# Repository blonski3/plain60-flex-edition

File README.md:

# Plain60 MX+ALPS Flex Edition rev2.2

This universal 60% PCB is designed to support as little layouts as possible without limiting usability for most users. The reason I did this is because other PCBs made for this form factor usually have so many supported layouts that it could almost qualify as swiss cheese.

It also features a fuse and an ESD protection chip to protect the MCU and other parts of the PCB.

## Features
- Fits in the TGR Unikorn
- Compatible with QMK Firmware and VIA Configurator (if you flash a VIA compatible .hex file)
- Compatible with most universal 60% cases and HHKB/WKL Tofu by KBDfans
- USB type-C
- Optional JST header for connection with daughterboard
- Footprint for optional speaker (AST1109MLTRQ)
- ESD protection and fuse
- No LEDs and no underglow
- Minimal layout support
- ISP header

## Supported layouts

## Building
If you feel like building a few of these PCBs yourself, go to the 'Releases' tab and download the latest gerber files. Order those at your favourite PCB manufacturer, get the components needed (see below) and solder them on! A hot air station is not required but a soldering iron is. Flux is recommended.

## Opening the project
To open the files you will need the latest KiCAD nightly version.

## Bill of materials (BOM)
Amount is per PCB, multiply as needed.

| LCSC part # | Description   | Value | Package  | Amount |
| ----------- | ------------- | ----- | -------- | ------:|
| C128353     | Capacitor     | 0.1uF | 0805     | 4      |
| C131056     | Capacitor     | 4.7uF | 0805     | 1      |
| C215803     | Capacitor     | 1uF   | 0805     | 1      |
| C109001     | Diode         |       | 0805     | 65     |
| C261942     | Fuse          |       | 0805     | 1      |
| C165948     | Connector     |       | SMD/THT  | 1      |
| C103904     | Resistor      | 10K   | 0805     | 2      |
| C212411     | Resistor      | 5.1K  | 0805     | 2      |
| C325772     | Resistor      | 22    | 0805     | 2      |
| C44854      | MCU           | 32U4  | QFP-44   | 1      |
| C7519       | ESD chip      |       | SOT23-6  | 1      |
| C341521     | Resonator     | 16MHz | SMD      | 1      |
| C92584      | Switch        |       | SMD      | 1      |
| C160404     | Optional JST  |       | SMD      | 1      |

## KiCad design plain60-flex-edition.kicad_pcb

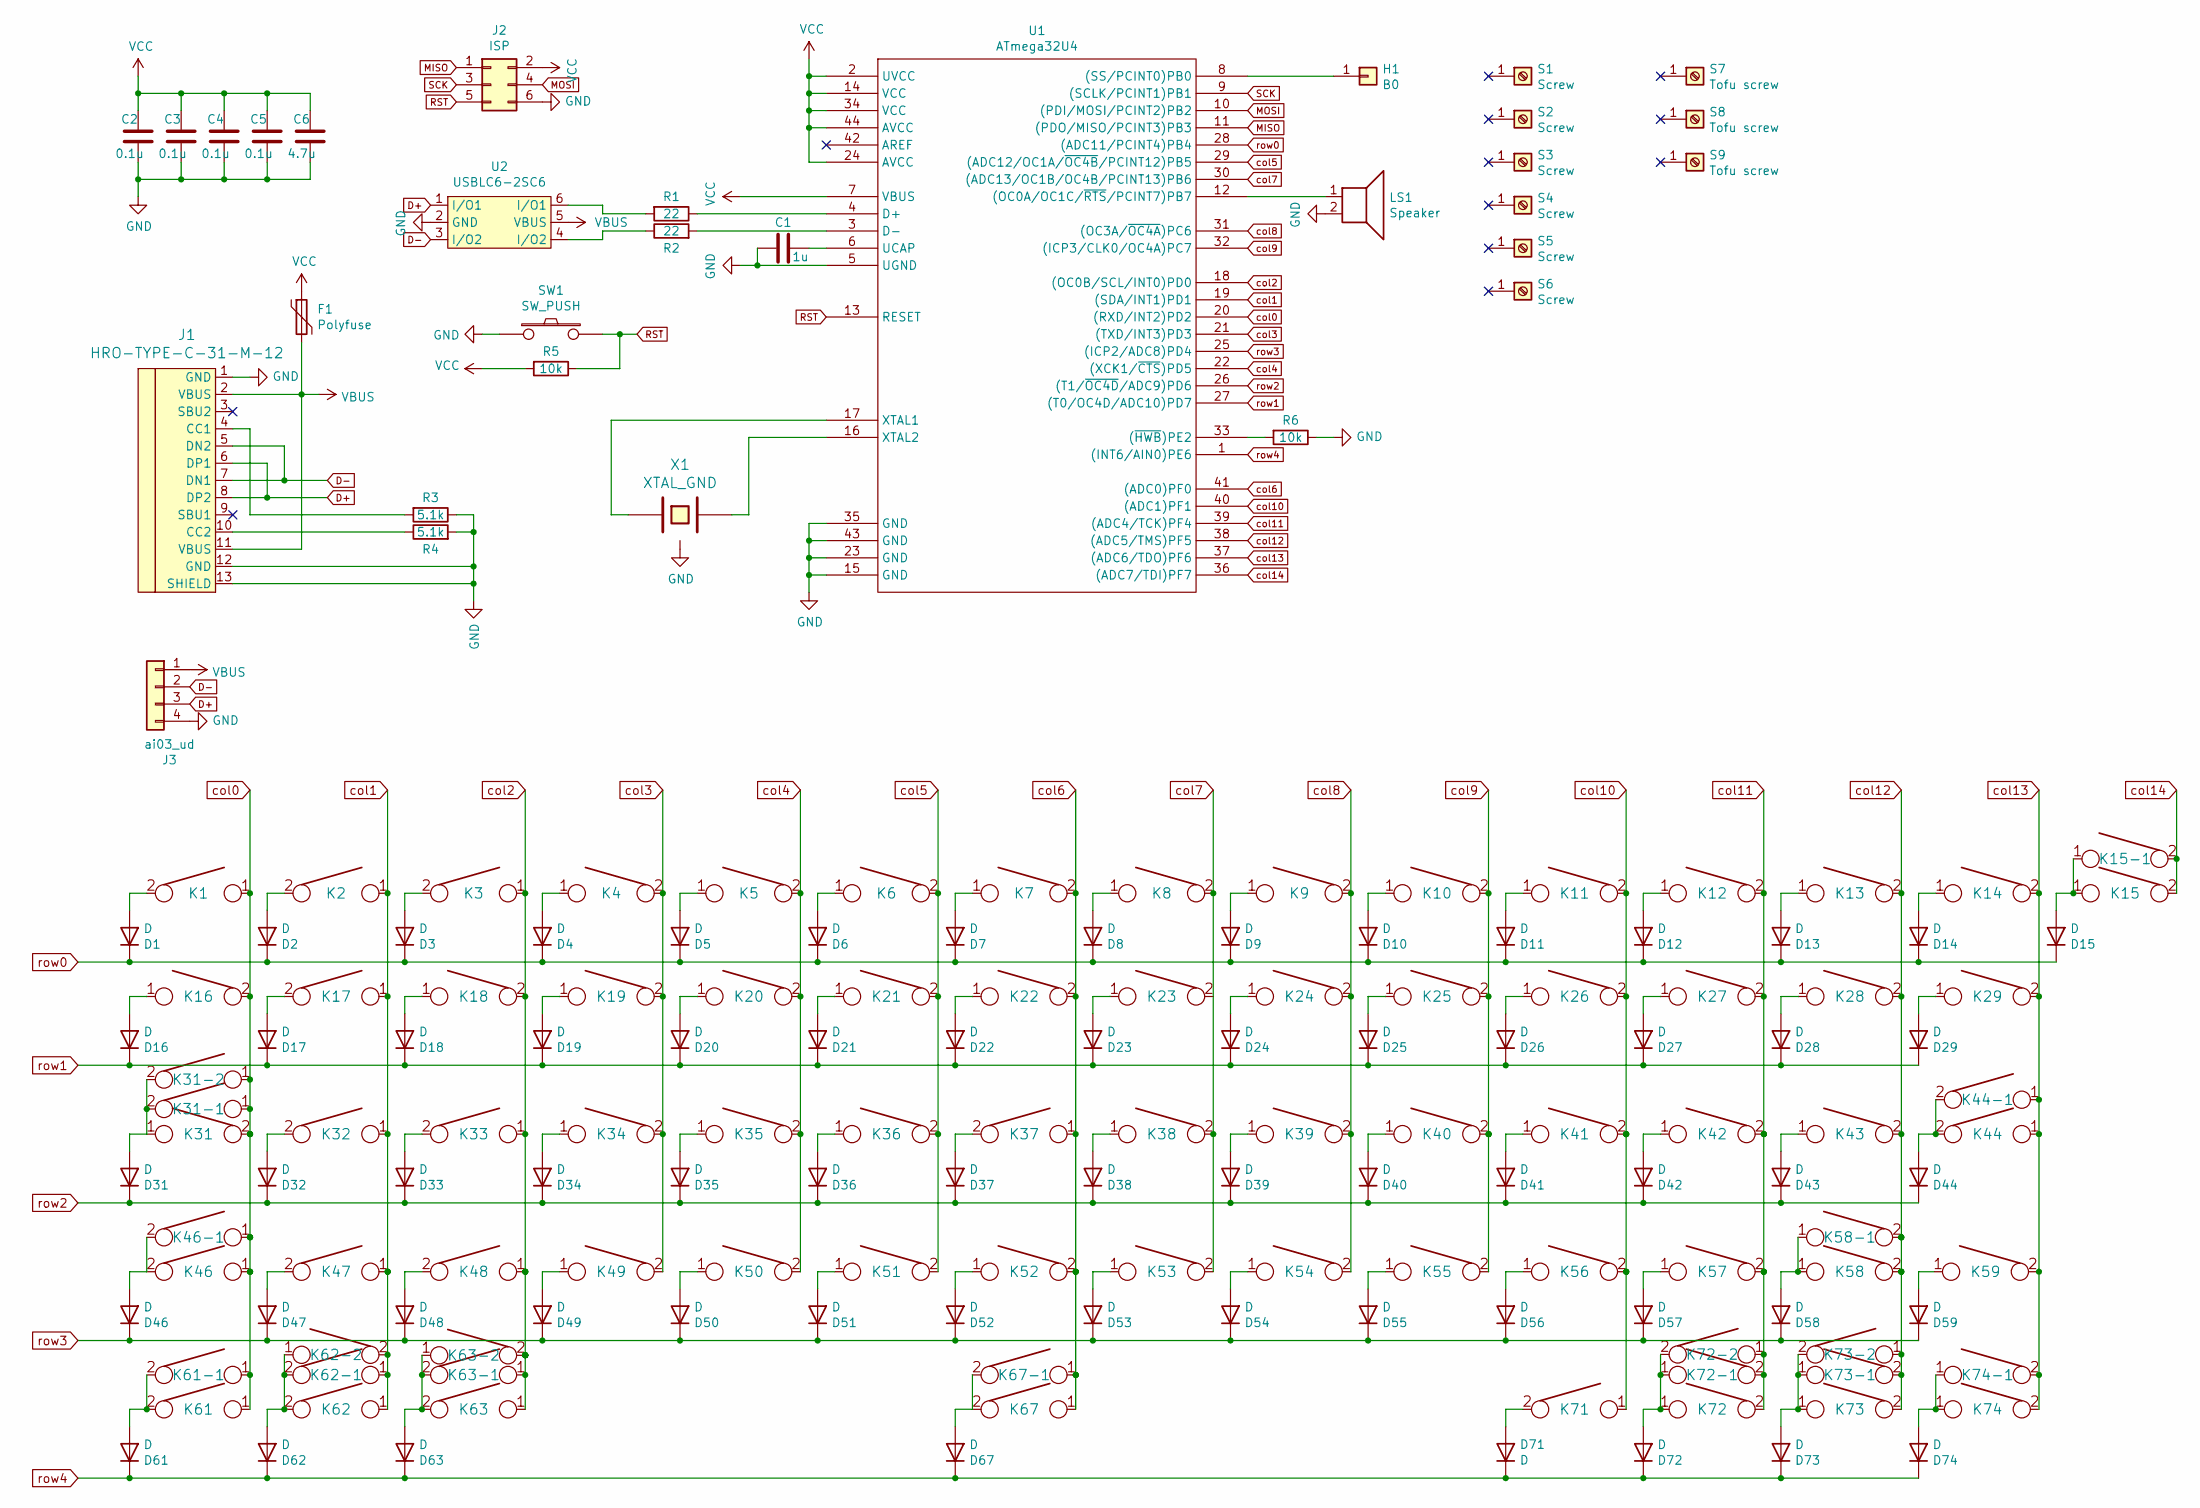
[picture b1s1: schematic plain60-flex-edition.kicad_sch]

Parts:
C1: 1u; C_0805
C2, C3, C4, C5: 0.1u; C_0805
C6: 4.7u; C_0805
D1, D2, D3, D4, D5, D6, D7, D8, D9, D10, D11, D12, D13, D14, D15, D16, D17, D18, D19, D20, D21, D22, D23, D24, D25, D26, D27, D28, D29, D31, D32, D33, D34, D35, D36, D37, D38, D39, D40, D41, D42, D43, D44, D46, D47, D48, D49, D50, D51, D52, D53, D54, D55, D56, D57, D58, D59, D61, D62, D63, D67, D71, D72, D73, D74: D; D_0805
F1: Polyfuse; R_0805
H1: B0; free_pin
J1: HRO-TYPE-C-31-M-12
J2: ISP; isp_standard
J3: ai03_ud; JST_SH_SM04B-SRSS-TB_1x04-1MP_P1.00mm_Horizontal
K1, K2, K3, K4, K5, K6, K7, K8, K9, K10, K11, K12, K13, K14, K15-1, K17, K18, K19, K20, K21, K22, K23, K24, K25, K26, K27, K28, K32, K33, K34, K35, K36, K37, K38, K39, K40, K41, K42, K47, K48, K49, K50, K51, K52, K53, K54, K55, K56, K57, K59, K62-1, K73-1: KEYSW; MX-1U-NoLED
K15: KEYSW; MX-2U-NoLED
K16, K29, K43, K61-1, K63-1, K72-1, K74-1: KEYSW; MX-1.5U-NoLED
K31, K58-1: KEYSW; MX-1.75U-NoLED
K31-1, K46-1, K61, K62, K63, K71, K72, K73, K74: KEYSW; MX-1.25U-NoLED
K31-2, K63-2, K72-2: KEYSW; ALPS-1.5U
K44, K46: KEYSW; MX-2.25U-NoLED
K44-1: KEYSW; MX-ISO-FLIPPED-ReversedStabilizers
K58: KEYSW; MX-2.75U-NoLED
K62-2, K73-2: KEYSW; ALPS-1.25U
K67: KEYSW; MX-6.25U-ReversedStabilizers-NoLED
K67-1: KEYSW; MX-7U-ReversedStabilizers-NoLED
LS1: Speaker; speaker_AST1109MLTRQ
R1, R2: 22; R_0805
R3, R4: 5.1k; R_0805
R5, R6: 10k; R_0805
S1, S2, S3, S6: Screw; 5.5_5x2.5mm
S4, S5: Screw; 10x5_7x2.5mm
S7, S8, S9: Tofu screw; 5.5_5x2.5mm
SW1: SW_PUSH; SW_SPST_TL3342
U1: ATmega32U4; ATMEGA32U4
U2: USBLC6-2SC6; Farnell 1295310
X1: XTAL_GND; Resonator_SMD_muRata_CSTNExxV-3Pin-p1.2

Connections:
D+: J1.6 (DP1), J1.8 (DP2), J3.3, U2.1 (I/O1)
D-: J1.5 (DN2), J1.7 (DN1), J3.2, U2.3 (I/O2)
GND: C1.2, C2.1, C3.1, C4.1, C5.1, C6.1, J1.1 (GND), J1.12 (GND), J1.13 (SHIELD), J2.6, J3.4, LS1.2, R3.1, R4.2, R6.1, SW1.1, U1.5 (UGND), U1.15 (GND), U1.23 (GND), U1.35 (GND), U1.43 (GND), U2.2 (GND), X1.3
MISO: J2.1, U1.11 ((PDO/MISO/PCINT3)PB3)
MOSI: J2.4, U1.10 ((PDI/MOSI/PCINT2)PB2)
unnamed: C1.1, U1.6 (UCAP)
unnamed: D1.2 (A), K1.2
unnamed: D2.2 (A), K2.2
unnamed: D3.2 (A), K3.2
unnamed: D4.2 (A), K4.1
unnamed: D5.2 (A), K5.1
unnamed: D6.2 (A), K6.1
unnamed: D7.2 (A), K7.1
unnamed: D8.2 (A), K8.1
unnamed: D9.2 (A), K9.1
unnamed: D10.2 (A), K10.1
unnamed: D11.2 (A), K11.1
unnamed: D12.2 (A), K12.1
unnamed: D13.2 (A), K13.1
unnamed: D14.2 (A), K14.1
unnamed: D15.2 (A), K15.1, K15-1.1
unnamed: D16.2 (A), K16.1
unnamed: D17.2 (A), K17.2
unnamed: D18.2 (A), K18.1
unnamed: D19.2 (A), K19.1
unnamed: D20.2 (A), K20.1
unnamed: D21.2 (A), K21.1
unnamed: D22.2 (A), K22.1
unnamed: D23.2 (A), K23.1
unnamed: D24.2 (A), K24.1
unnamed: D25.2 (A), K25.1
unnamed: D26.2 (A), K26.1
unnamed: D27.2 (A), K27.1
unnamed: D28.2 (A), K28.1
unnamed: D29.2 (A), K29.1
unnamed: D31.2 (A), K31.1, K31-1.2, K31-2.2
unnamed: D32.2 (A), K32.2
unnamed: D33.2 (A), K33.2
unnamed: D34.2 (A), K34.1
unnamed: D35.2 (A), K35.1
unnamed: D36.2 (A), K36.1
unnamed: D37.2 (A), K37.2
unnamed: D38.2 (A), K38.1
unnamed: D39.2 (A), K39.1
unnamed: D40.2 (A), K40.1
unnamed: D41.2 (A), K41.1
unnamed: D42.2 (A), K42.1
unnamed: D43.2 (A), K43.1
unnamed: D44.2 (A), K44.2, K44-1.2
unnamed: D47.2 (A), K47.2
unnamed: D48.2 (A), K48.2
unnamed: D49.2 (A), K49.1
unnamed: D50.2 (A), K50.1
unnamed: D51.2 (A), K51.1
unnamed: D52.2 (A), K52.1
unnamed: D53.2 (A), K53.1
unnamed: D54.2 (A), K54.1
unnamed: D55.2 (A), K55.1
unnamed: D56.2 (A), K56.1
unnamed: D57.2 (A), K57.1
unnamed: D58.2 (A), K58.1, K58-1.1
unnamed: D62.2 (A), K62.2, K62-1.2, K62-2.1
unnamed: D63.2 (A), K63.2, K63-1.2, K63-2.1
unnamed: D67.2 (A), K67.2, K67-1.2
unnamed: D71.2 (A), K71.2
unnamed: D72.2 (A), K72.1, K72-1.1, K72-2.2
unnamed: D73.2 (A), K73.1, K73-1.1, K73-2.2
unnamed: D74.2 (A), K74.1, K74-1.1
unnamed: H1.1, U1.8 ((SS/PCINT0)PB0)
unnamed: J1.4 (CC1), R3.2
unnamed: J1.10 (CC2), R4.1
unnamed: D46.2 (A), K46.2, K46-1.2
unnamed: D59.2 (A), K59.1
unnamed: D61.2 (A), K61.2, K61-1.2
unnamed: LS1.1, U1.12 ((OC0A/OC1C/~RTS/PCINT7)PB7)
unnamed: R1.1, U1.4 (D+)
unnamed: R1.2, U2.6 (I/O1)
unnamed: R2.1, U2.4 (I/O2)
unnamed: R2.2, U1.3 (D-)
unnamed: R6.2, U1.33 ((~HWB)PE2)
unnamed: U1.16 (XTAL2), X1.2
unnamed: U1.17 (XTAL1), X1.1
RST: J2.5, R5.1, SW1.2, U1.13 (RESET)
SCK: J2.3, U1.9 ((SCLK/PCINT1)PB1)
VBUS: F1.2, J1.2 (VBUS), J1.11 (VBUS), J3.1, U2.5 (VBUS)
VCC: C2.2, C3.2, C4.2, C5.2, C6.2, F1.1, J2.2, R5.2, U1.2 (UVCC), U1.7 (VBUS), U1.14 (VCC), U1.24 (AVCC), U1.34 (VCC), U1.44 (AVCC)
col0: K1.1, K16.2, K31.2, K31-1.1, K31-2.1, K46.1, K46-1.1, K61.1, K61-1.1, U1.20 ((RXD/INT2)PD2)
col1: K2.1, K17.1, K32.1, K47.1, K62.1, K62-1.1, K62-2.2, U1.19 ((SDA/INT1)PD1)
col2: K3.1, K18.2, K33.1, K48.1, K63.1, K63-1.1, K63-2.2, U1.18 ((OC0B/SCL/INT0)PD0)
col3: K4.2, K19.2, K34.2, K49.2, U1.21 ((TXD/INT3)PD3)
col4: K5.2, K20.2, K35.2, K50.2, U1.22 ((XCK1/~CTS)PD5)
col5: K6.2, K21.2, K36.2, K51.2, U1.29 ((ADC12/OC1A/~OC4B/PCINT12)PB5)
col6: K7.2, K22.2, K37.1, K52.2, K67.1, K67-1.1, U1.41 ((ADC0)PF0)
col7: K8.2, K38.2, K53.2, U1.30 ((ADC13/OC1B/OC4B/PCINT13)PB6)
col8: K9.2, K24.2, K39.2, K54.2, U1.31 ((OC3A/~OC4A)PC6)
col9: K10.2, K25.2, K40.2, K55.2, U1.32 ((ICP3/CLK0/OC4A)PC7)
col10: K11.2, K26.2, K41.2, K56.2, K71.1, U1.40 ((ADC1)PF1)
col11: K12.2, K27.2, K42.2, K57.2, K72.2, K72-1.2, K72-2.1, U1.39 ((ADC4/TCK)PF4)
col12: K13.2, K28.2, K43.2, K58.2, K58-1.2, K73.2, K73-1.2, K73-2.1, U1.38 ((ADC5/TMS)PF5)
col13: K14.2, K29.2, K44.1, K44-1.1, K59.2, K74.2, K74-1.2, U1.37 ((ADC6/TDO)PF6)
col14: K15.2, K15-1.2, U1.36 ((ADC7/TDI)PF7)
row0: D1.1 (K), D2.1 (K), D3.1 (K), D4.1 (K), D5.1 (K), D6.1 (K), D7.1 (K), D8.1 (K), D9.1 (K), D10.1 (K), D11.1 (K), D12.1 (K), D13.1 (K), D14.1 (K), D15.1 (K), U1.28 ((ADC11/PCINT4)PB4)
row1: D16.1 (K), D17.1 (K), D18.1 (K), D19.1 (K), D20.1 (K), D21.1 (K), D22.1 (K), D23.1 (K), D24.1 (K), D25.1 (K), D26.1 (K), D27.1 (K), D28.1 (K), D29.1 (K), U1.27 ((T0/OC4D/ADC10)PD7)
row2: D31.1 (K), D32.1 (K), D33.1 (K), D34.1 (K), D35.1 (K), D36.1 (K), D37.1 (K), D38.1 (K), D39.1 (K), D40.1 (K), D41.1 (K), D42.1 (K), D43.1 (K), D44.1 (K), U1.26 ((T1/~OC4D/ADC9)PD6)
row3: D46.1 (K), D47.1 (K), D48.1 (K), D49.1 (K), D50.1 (K), D51.1 (K), D52.1 (K), D53.1 (K), D54.1 (K), D55.1 (K), D56.1 (K), D57.1 (K), D58.1 (K), D59.1 (K), U1.25 ((ICP2/ADC8)PD4)
row4: D61.1 (K), D62.1 (K), D63.1 (K), D67.1 (K), D71.1 (K), D72.1 (K), D73.1 (K), D74.1 (K), U1.1 ((INT6/AIN0)PE6)

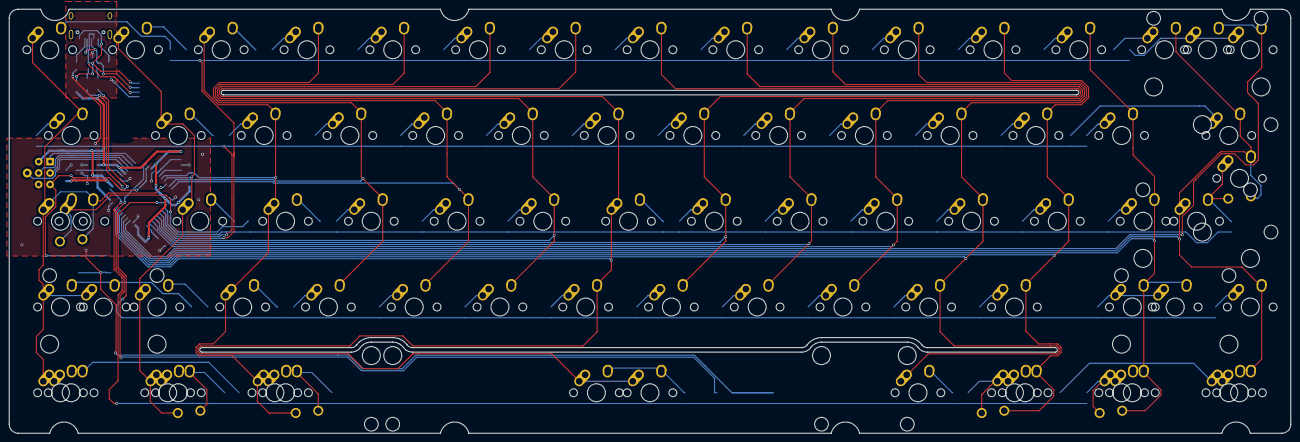
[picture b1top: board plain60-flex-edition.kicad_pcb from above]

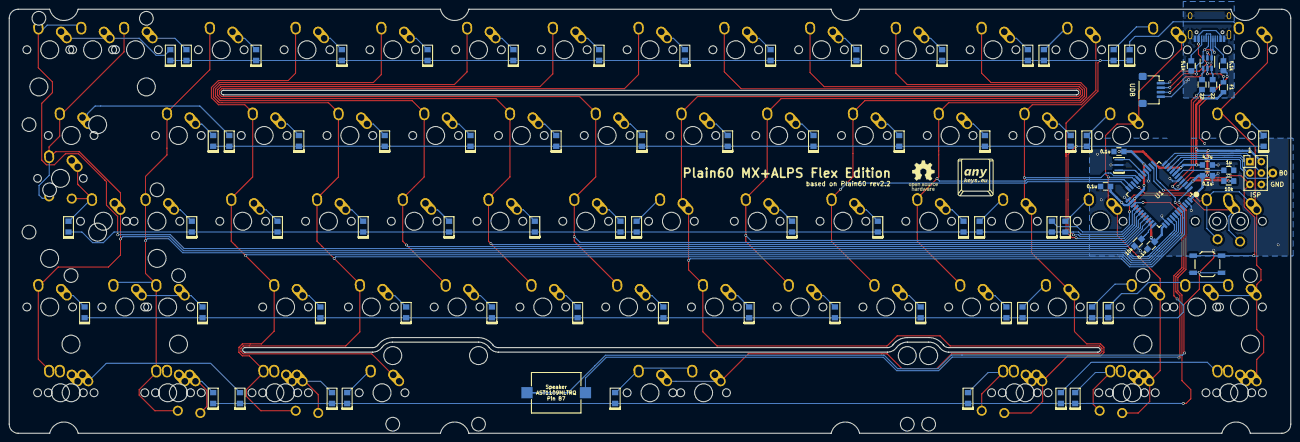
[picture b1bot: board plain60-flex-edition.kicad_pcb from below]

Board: 2 copper layers, 284.7 x 94.2 mm, 178 parts (87 on the bottom side), 106 nets.

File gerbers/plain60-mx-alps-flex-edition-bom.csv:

Comment,Designator,Footprint,JLCPCB Part #（optional）
1u,C1,C_0805,C215803
0.1u,"C4,C5,C2,C3",C_0805,C128353
4.7u,C6,C_0805,C131056
D,"D73,D72,D71,D67,D63,D59,D58,D57,D56,D53,D51,D50,D27,D42,D18,D25,D41,D36,D31,D40,D37,D32,D34,D21,D26,D22,D24,D43,D38,D35,D48,D54,D44,D62,D39,D20,D28,D33,D23,D55,D52,D19,D10,D14,D9,D13,D11,D15,D17,D16,D12,D7,D3,D5,D8,D6,D4,D74,D49,D46,D29,D1,D47,D2,D61",D_0805,C109001
Polyfuse,F1,R_0805,C261942
HRO-TYPE-C-31-M-12,J1,HRO-TYPE-C-31-M-12,C165948
ai03_ud,J3,JST_SH_SM04B-SRSS-TB_1x04-1MP_P1.00mm_Horizontal,C160404
22,"R1,R2",R_0805,C413250
5.1k,"R4,R3",R_0805,C212411
10k,"R6,R5",R_0805,C103904
SW_PUSH,SW1,SW_SPST_TL3342,C92584
ATmega32U4,U1,ATMEGA32U4,C44854
USBLC6-2SC6,U2,USBLC6-2SC6,C7519
XTAL_GND,X1,Resonator_SMD_muRata_CSTNExxV-3Pin-p1.2,C341521

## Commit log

2022-02-10 Add submodules
2022-02-10 Footprints from plain60-alps-flex-edition
2022-02-10 Updated libraries
2022-02-10 Footprints exported from PCB files
2022-02-10 Update libraries
2022-02-10 Change footprints to MX+ALPS
2022-02-10 Add AEK support
2022-02-10 Upload files
2022-02-10 JLC files
